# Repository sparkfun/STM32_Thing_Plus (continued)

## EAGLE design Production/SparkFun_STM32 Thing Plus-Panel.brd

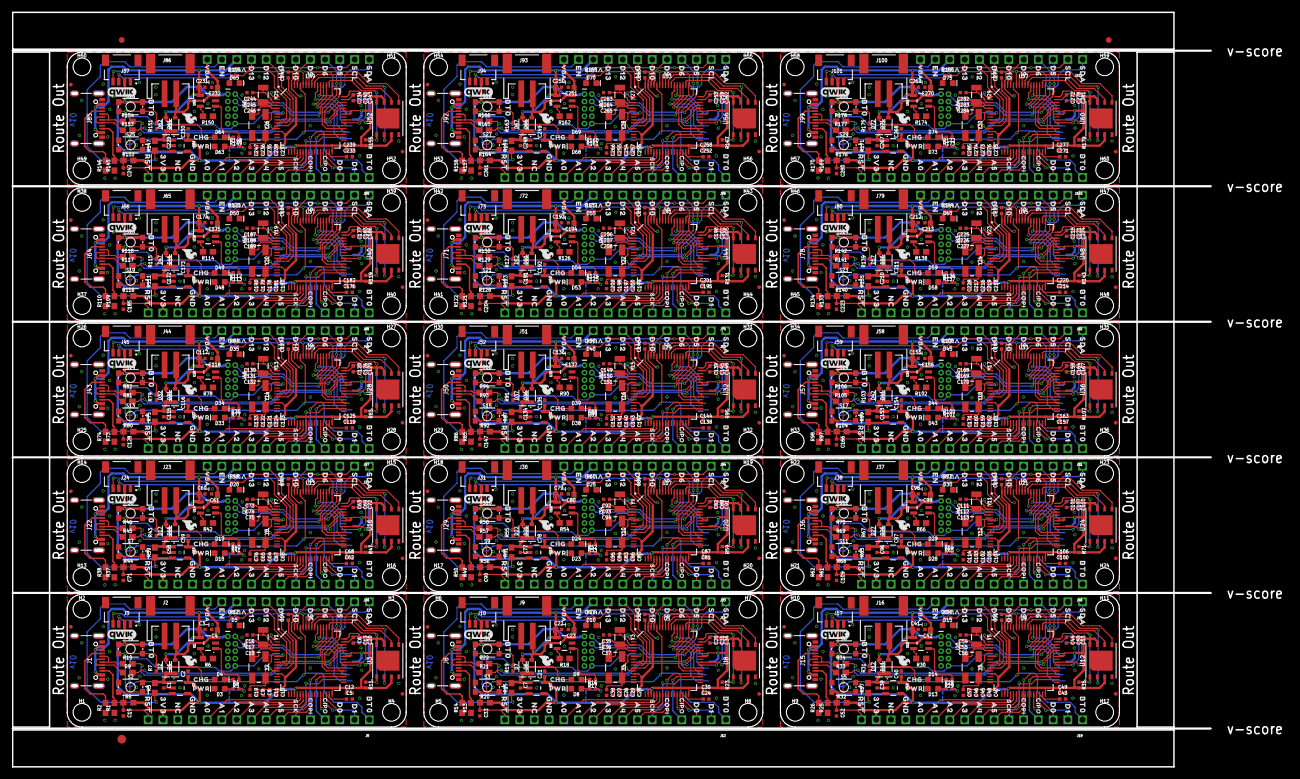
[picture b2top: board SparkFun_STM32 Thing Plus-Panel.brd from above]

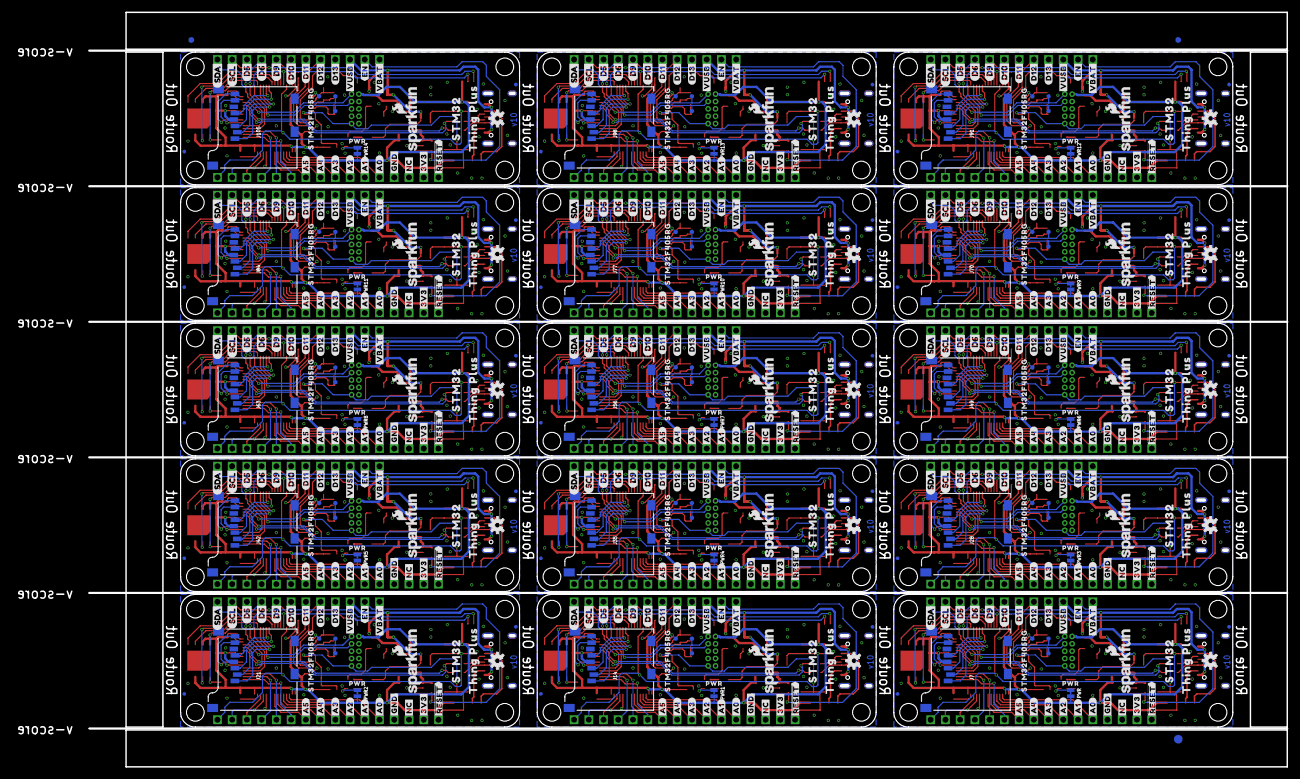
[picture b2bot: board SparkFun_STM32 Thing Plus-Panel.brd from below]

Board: 2 copper layers, 206.5 x 130.0 mm, 1866 parts (528 on the bottom side), 885 nets.

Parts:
C1, C2, C7, C9, C21, C27, C39, C40, C46, C58, C59, C65, C77, C78, C84, C96, C97, C103, C115, C116, C122, C134, C135, C141, C153, C154, C160, C172, C173, C179, C191, C192, C198, C210, C211, C217, C229, C230, C236, C248, C249, C255, C267, C268, C274: 1.0uF; 0402-TIGHT
C3, C4, C10, C22, C23, C28, C41, C42, C47, C60, C61, C66, C79, C80, C85, C98, C99, C104, C117, C118, C123, C136, C137, C142, C155, C156, C161, C174, C175, C180, C193, C194, C199, C212, C213, C218, C231, C232, C237, C250, C251, C256, C269, C270, C275: 4.7uF; 0402-TIGHT
C5, C6, C24, C25, C43, C44, C62, C63, C81, C82, C100, C101, C119, C120, C138, C139, C157, C158, C176, C177, C195, C196, C214, C215, C233, C234, C252, C253, C271, C272: 2.2uF; 0402-TIGHT
C8, C11, C12, C13, C14, C15, C20, C26, C29, C30, C31, C32, C33, C34, C45, C48, C49, C50, C51, C52, C53, C64, C67, C68, C69, C70, C71, C72, C83, C86, C87, C88, C89, C90, C91, C102, C105, C106, C107, C108, C109, C110, C121, C124, C125, C126, C127, C128, C129, C140, C143, C144, C145, C146, C147, C148, C159, C162, C163, C164, C165, C166, C167, C178, C181, C182, C183, C184, C185, C186, C197, C200, C201, C202, C203, C204, C205, C216, C219, C220, C221, C222, C223, C224, C235, C238, C239, C240, C241, C242, C243, C254, C257, C258, C259, C260, C261, C262, C273, C276, C277, C278, C279, C280, C281: 0.1uF; 0402-TIGHT
C16, C17, C35, C36, C54, C55, C73, C74, C92, C93, C111, C112, C130, C131, C149, C150, C168, C169, C187, C188, C206, C207, C225, C226, C244, C245, C263, C264, C282, C283: 15pF; 0402-TIGHT
C18, C19, C37, C38, C56, C57, C75, C76, C94, C95, C113, C114, C132, C133, C151, C152, C170, C171, C189, C190, C208, C209, C227, C228, C246, C247, C265, C266, C284, C285: 22pF; 0402-TIGHT
D1, D2, D6, D7, D11, D12, D16, D17, D21, D22, D26, D27, D31, D32, D36, D37, D41, D42, D46, D47, D51, D52, D56, D57, D61, D62, D66, D67, D71, D72: 3A/10V/280mV; SOD-323
D3, D8, D13, D18, D23, D28, D33, D38, D43, D48, D53, D58, D63, D68, D73: RED; LED-0603
D4, D9, D14, D19, D24, D29, D34, D39, D44, D49, D54, D59, D64, D69, D74: Yellow; LED-0603
D5, D10, D15, D20, D25, D30, D35, D40, D45, D50, D55, D60, D65, D70, D75: BLUE; LED-0603
E$1, E$2, E$3, E$4: FIDUCIAL-1X2
E$5, E$6: FIDUCIAL-1.5X3
FD1, FD2, FD3, FD4, FD5, FD6, FD7, FD8, FD9, FD10, FD11, FD12, FD13, FD14, FD15, FD16, FD17, FD18, FD19, FD20, FD21, FD22, FD23, FD24, FD25, FD26, FD27, FD28, FD29, FD30, FD31, FD32, FD33, FD34, FD35, FD36, FD37, FD38, FD39, FD40, FD41, FD42, FD43, FD44, FD45, FD46, FD47, FD48, FD49, FD50, FD51, FD52, FD53, FD54, FD55, FD56, FD57, FD58, FD59, FD60: FIDUCIALUFIDUCIAL; FIDUCIAL-MICRO
H1, H2, H3, H4, H5, H6, H7, H8, H9, H10, H11, H12, H13, H14, H15, H16, H17, H18, H19, H20, H21, H22, H23, H24, H25, H26, H27, H28, H29, H30, H31, H32, H33, H34, H35, H36, H37, H38, H39, H40, H41, H42, H43, H44, H45, H46, H47, H48, H49, H50, H51, H52, H53, H54, H55, H56, H57, H58, H59, H60: STAND-OFFTIGHT; STAND-OFF-TIGHT
J1, J8, J15, J22, J29, J36, J43, J50, J57, J64, J71, J78, J85, J92, J99: USB-C-16P-2LAYER-PADS
J2, J9, J16, J23, J30, J37, J44, J51, J58, J65, J72, J79, J86, J93, J100: JST-2-SMD
J3, J10, J17, J24, J31, J38, J45, J52, J59, J66, J73, J80, J87, J94, J101: QWIIC_RA; JST04_1MM_RA
J4, J11, J18, J25, J32, J39, J46, J53, J60, J67, J74, J81, J88, J95, J102: 1X12_SM_SQ_NOSILK
J5, J12, J19, J26, J33, J40, J47, J54, J61, J68, J75, J82, J89, J96, J103: 1X16_SM_SQ_NOSILK
J6, J13, J20, J27, J34, J41, J48, J55, J62, J69, J76, J83, J90, J97, J104: CORTEX_DEBUG; 2X5-PTH-1.27MM-NO_SILK
J7, J14, J21, J28, J35, J42, J49, J56, J63, J70, J77, J84, J91, J98, J105: MICRO-SD; MICRO-SD-SOCKET
LOGO1, LOGO4, LOGO7, LOGO10, LOGO13, LOGO16, LOGO19, LOGO22, LOGO25, LOGO28, LOGO31, LOGO34, LOGO37, LOGO40, LOGO43: QWIIC_LOGO_5MM; QWIIC_5MM
LOGO2, LOGO5, LOGO8, LOGO11, LOGO14, LOGO17, LOGO20, LOGO23, LOGO26, LOGO29, LOGO32, LOGO35, LOGO38, LOGO41, LOGO44: SFE_LOGO_NAME_FLAME.1_INCH; SFE_LOGO_NAME_FLAME_.1
LOGO3, LOGO6, LOGO9, LOGO12, LOGO15, LOGO18, LOGO21, LOGO24, LOGO27, LOGO30, LOGO33, LOGO36, LOGO39, LOGO42, LOGO45: OSHW-LOGOS; OSHW-LOGO-S
PWR, PWR1, PWR2, PWR3, PWR4, PWR5, PWR6, PWR7, PWR8, PWR9, PWR10, PWR11, PWR12, PWR13, PWR14: SMT-JUMPER_2_NC_TRACE_NO-SILK
R1, R2, R13, R14, R25, R26, R37, R38, R49, R50, R61, R62, R73, R74, R85, R86, R97, R98, R109, R110, R121, R122, R133, R134, R145, R146, R157, R158, R169, R170: 5.1k; 0603
R3, R15, R27, R39, R51, R63, R75, R87, R99, R111, R123, R135, R147, R159, R171: 10k; 0603
R4, R5, R12, R16, R17, R24, R28, R29, R36, R40, R41, R48, R52, R53, R60, R64, R65, R72, R76, R77, R84, R88, R89, R96, R100, R101, R108, R112, R113, R120, R124, R125, R132, R136, R137, R144, R148, R149, R156, R160, R161, R168, R172, R173, R180: 1k; 0402-TIGHT
R6, R18, R30, R42, R54, R66, R78, R90, R102, R114, R126, R138, R150, R162, R174: 2.0k; 0603
R7, R11, R19, R23, R31, R35, R43, R47, R55, R59, R67, R71, R79, R83, R91, R95, R103, R107, R115, R119, R127, R131, R139, R143, R151, R155, R163, R167, R175, R179: 100k; 0402-TIGHT
R8, R20, R32, R44, R56, R68, R80, R92, R104, R116, R128, R140, R152, R164, R176: 4.7k; 0603
R9, R10, R21, R22, R33, R34, R45, R46, R57, R58, R69, R70, R81, R82, R93, R94, R105, R106, R117, R118, R129, R130, R141, R142, R153, R154, R165, R166, R177, R178: 22; 0603
S1, S2, S3, S4, S5, S6, S7, S8, S9, S10, S11, S12, S13, S14, S15, S16, S17, S18, S19, S20, S21, S22, S23, S24, S25, S26, S27, S28, S29, S30: TACTILE_SWITCH_SMD_4.6X2.8MM
TP1, TP2, TP3, TP4, TP5, TP6, TP7, TP8, TP9, TP10, TP11, TP12, TP13, TP14, TP15, TP16, TP17, TP18, TP19, TP20, TP21, TP22, TP23, TP24, TP25, TP26, TP27, TP28, TP29, TP30: PAD.03X.03
U1, U6, U10, U14, U18, U22, U26, U30, U34, U38, U42, U46, U50, U54, U58: MCP73831; SOT23-5
U2, U7, U11, U15, U19, U23, U27, U31, U35, U39, U43, U47, U51, U55, U59: 3.3V; SOT23-5
U3, U8, U12, U16, U20, U24, U28, U32, U36, U40, U44, U48, U52, U56, U60: W25QXX128MBIT-6X5; WSON-8-6X5
U4, U5, U9, U13, U17, U21, U25, U29, U33, U37, U41, U45, U49, U53, U57: STM32F405RGT6; TQFP64
U$1, U$111, U$169, U$227, U$285, U$343, U$401, U$459, U$517, U$575, U$633, U$691, U$749, U$807, U$865: D53
U$2, U$17, U$117, U$175, U$233, U$291, U$349, U$407, U$465, U$523, U$581, U$639, U$697, U$755, U$813: #RST#0
U$3, U$49, U$90, U$97, U$148, U$155, U$206, U$213, U$264, U$271, U$322, U$329, U$380, U$387, U$438, U$445, U$496, U$503, U$554, U$561, U$612, U$619, U$670, U$677, U$728, U$735, U$786, U$793, U$844, U$851: BT00
U$4, U$18, U$118, U$176, U$234, U$292, U$350, U$408, U$466, U$524, U$582, U$640, U$698, U$756, U$814: D130
U$5, U$19, U$58, U$101, U$119, U$159, U$177, U$217, U$235, U$275, U$293, U$333, U$351, U$391, U$409, U$449, U$467, U$507, U$525, U$565, U$583, U$623, U$641, U$681, U$699, U$739, U$757, U$797, U$815, U$855: PWR0
U$6, U$20, U$120, U$178, U$236, U$294, U$352, U$410, U$468, U$526, U$584, U$642, U$700, U$758, U$816: CHG0
U$7, U$21, U$121, U$179, U$237, U$295, U$353, U$411, U$469, U$527, U$585, U$643, U$701, U$759, U$817: ##RESET##0
U$8, U$22, U$122, U$180, U$238, U$296, U$354, U$412, U$470, U$528, U$586, U$644, U$702, U$760, U$818: #3V3#0
U$9, U$28, U$123, U$181, U$239, U$297, U$355, U$413, U$471, U$529, U$587, U$645, U$703, U$761, U$819: #NC#0
U$10, U$66, U$124, U$182, U$240, U$298, U$356, U$414, U$472, U$530, U$588, U$646, U$704, U$762, U$820: #GND#0
U$11, U$67, U$125, U$183, U$241, U$299, U$357, U$415, U$473, U$531, U$589, U$647, U$705, U$763, U$821: #A0#0
U$12, U$68, U$126, U$184, U$242, U$300, U$358, U$416, U$474, U$532, U$590, U$648, U$706, U$764, U$822: #A1#0
U$13, U$69, U$127, U$185, U$243, U$301, U$359, U$417, U$475, U$533, U$591, U$649, U$707, U$765, U$823: #A2#0
U$14, U$70, U$128, U$186, U$244, U$302, U$360, U$418, U$476, U$534, U$592, U$650, U$708, U$766, U$824: #A3#0
U$15, U$71, U$129, U$187, U$245, U$303, U$361, U$419, U$477, U$535, U$593, U$651, U$709, U$767, U$825: #A4#0
U$16, U$72, U$130, U$188, U$246, U$304, U$362, U$420, U$478, U$536, U$594, U$652, U$710, U$768, U$826: #A5#0
U$23, U$112, U$170, U$228, U$286, U$344, U$402, U$460, U$518, U$576, U$634, U$692, U$750, U$808, U$866: D62
U$24, U$113, U$171, U$229, U$287, U$345, U$403, U$461, U$519, U$577, U$635, U$693, U$751, U$809, U$867: D91
U$25, U$55, U$94, U$114, U$152, U$172, U$210, U$230, U$268, U$288, U$326, U$346, U$384, U$404, U$442, U$462, U$500, U$520, U$558, U$578, U$616, U$636, U$674, U$694, U$732, U$752, U$790, U$810, U$848, U$868: D100
U$26, U$115, U$173, U$231, U$289, U$347, U$405, U$463, U$521, U$579, U$637, U$695, U$753, U$811, U$869: SCL4
U$27, U$116, U$174, U$232, U$290, U$348, U$406, U$464, U$522, U$580, U$638, U$696, U$754, U$812, U$870: SDA5
U$29, U$73, U$131, U$189, U$247, U$305, U$363, U$421, U$479, U$537, U$595, U$653, U$711, U$769, U$827: #D11#0
U$30, U$74, U$132, U$190, U$248, U$306, U$364, U$422, U$480, U$538, U$596, U$654, U$712, U$770, U$828: #D12#0
U$31, U$75, U$133, U$191, U$249, U$307, U$365, U$423, U$481, U$539, U$597, U$655, U$713, U$771, U$829: #D13#0
U$32, U$76, U$134, U$192, U$250, U$308, U$366, U$424, U$482, U$540, U$598, U$656, U$714, U$772, U$830: #VUSB#0
U$33, U$77, U$135, U$193, U$251, U$309, U$367, U$425, U$483, U$541, U$599, U$657, U$715, U$773, U$831: #EN#0
U$34, U$78, U$136, U$194, U$252, U$310, U$368, U$426, U$484, U$542, U$600, U$658, U$716, U$774, U$832: #VBAT#0
U$35, U$79, U$137, U$195, U$253, U$311, U$369, U$427, U$485, U$543, U$601, U$659, U$717, U$775, U$833: 3V30
U$36, U$80, U$138, U$196, U$254, U$312, U$370, U$428, U$486, U$544, U$602, U$660, U$718, U$776, U$834: NC0
U$37, U$81, U$139, U$197, U$255, U$313, U$371, U$429, U$487, U$545, U$603, U$661, U$719, U$777, U$835: GND0
U$38, U$82, U$140, U$198, U$256, U$314, U$372, U$430, U$488, U$546, U$604, U$662, U$720, U$778, U$836: A00
U$39, U$83, U$141, U$199, U$257, U$315, U$373, U$431, U$489, U$547, U$605, U$663, U$721, U$779, U$837: A10
U$40, U$84, U$142, U$200, U$258, U$316, U$374, U$432, U$490, U$548, U$606, U$664, U$722, U$780, U$838: A20
U$41, U$85, U$143, U$201, U$259, U$317, U$375, U$433, U$491, U$549, U$607, U$665, U$723, U$781, U$839: A30
U$42, U$86, U$144, U$202, U$260, U$318, U$376, U$434, U$492, U$550, U$608, U$666, U$724, U$782, U$840: A40
U$43, U$87, U$145, U$203, U$261, U$319, U$377, U$435, U$493, U$551, U$609, U$667, U$725, U$783, U$841: A50
U$44, U$98, U$156, U$214, U$272, U$330, U$388, U$446, U$504, U$562, U$620, U$678, U$736, U$794, U$852: SCK0
U$45, U$99, U$157, U$215, U$273, U$331, U$389, U$447, U$505, U$563, U$621, U$679, U$737, U$795, U$853: COPI0
U$46, U$100, U$158, U$216, U$274, U$332, U$390, U$448, U$506, U$564, U$622, U$680, U$738, U$796, U$854: CIPO0
U$47, U$88, U$146, U$204, U$262, U$320, U$378, U$436, U$494, U$552, U$610, U$668, U$726, U$784, U$842: D00
U$48, U$89, U$147, U$205, U$263, U$321, U$379, U$437, U$495, U$553, U$611, U$669, U$727, U$785, U$843: D10
U$50, U$104, U$162, U$220, U$278, U$336, U$394, U$452, U$510, U$568, U$626, U$684, U$742, U$800, U$858: VBAT_0
U$51, U$105, U$163, U$221, U$279, U$337, U$395, U$453, U$511, U$569, U$627, U$685, U$743, U$801, U$859: EN_0
U$52, U$91, U$149, U$207, U$265, U$323, U$381, U$439, U$497, U$555, U$613, U$671, U$729, U$787, U$845: D50
U$53, U$92, U$150, U$208, U$266, U$324, U$382, U$440, U$498, U$556, U$614, U$672, U$730, U$788, U$846: D60
U$54, U$93, U$151, U$209, U$267, U$325, U$383, U$441, U$499, U$557, U$615, U$673, U$731, U$789, U$847: D90
U$56, U$95, U$153, U$211, U$269, U$327, U$385, U$443, U$501, U$559, U$617, U$675, U$733, U$791, U$849: D110
U$57, U$96, U$154, U$212, U$270, U$328, U$386, U$444, U$502, U$560, U$618, U$676, U$734, U$792, U$850: D120
U$59, U$102, U$160, U$218, U$276, U$334, U$392, U$450, U$508, U$566, U$624, U$682, U$740, U$798, U$856: SCL_0
U$60, U$103, U$161, U$219, U$277, U$335, U$393, U$451, U$509, U$567, U$625, U$683, U$741, U$799, U$857: SDA_0
U$61, U$106, U$164, U$222, U$280, U$338, U$396, U$454, U$512, U$570, U$628, U$686, U$744, U$802, U$860: VUSB0
U$62, U$107, U$165, U$223, U$281, U$339, U$397, U$455, U$513, U$571, U$629, U$687, U$745, U$803, U$861: STM320
U$63, U$108, U$166, U$224, U$282, U$340, U$398, U$456, U$514, U$572, U$630, U$688, U$746, U$804, U$862: THING_PLUS0
U$64, U$109, U$167, U$225, U$283, U$341, U$399, U$457, U$515, U$573, U$631, U$689, U$747, U$805, U$863: STM32F405RG0
U$65, U$110, U$168, U$226, U$284, U$342, U$400, U$458, U$516, U$574, U$632, U$690, U$748, U$806, U$864: SFE_LOGO_FLAME_.1
VB, VB1, VB2, VB3, VB4, VB5, VB6, VB7, VB8, VB9, VB10, VB11, VB12, VB13, VB14: PAD.03X.03
Y1, Y3, Y5, Y7, Y9, Y11, Y13, Y15, Y17, Y19, Y21, Y23, Y25, Y27, Y29: 32.768kHz; CRYSTAL-SMD-3.2X1.5MM
Y2, Y4, Y6, Y8, Y10, Y12, Y14, Y16, Y18, Y20, Y22, Y24, Y26, Y28, Y30: 12MHz; CRYSTAL-SMD-5X3.2-4PAD

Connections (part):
3.3V: C2.1, C8.1, C9.1, C10.1, C11.1, C12.1, C13.1, C14.1, C20.1, J3.2, J5.15, J6.1, J7.VCC, PWR.2, R8.2, R11.2, S1.3, S1.4, U2.5, U3.3, U3.7, U3.8, U4.13, U4.19, U4.32, U4.42, U4.43, U4.48, U4.64
3.3V1: C21.1, C26.1, C27.1, C28.1, C29.1, C30.1, C31.1, C32.1, C34.1, J10.2, J12.15, J13.1, J14.VCC, PWR1.2, R20.2, R23.2, S4.3, S4.4, U5.13, U5.19, U5.32, U5.42, U5.43, U5.48, U5.64, U7.5, U8.3, U8.7, U8.8
3.3V2: C40.1, C45.1, C46.1, C47.1, C48.1, C49.1, C50.1, C51.1, C53.1, J17.2, J19.15, J20.1, J21.VCC, PWR2.2, R32.2, R35.2, S6.3, S6.4, U9.13, U9.19, U9.32, U9.42, U9.43, U9.48, U9.64, U11.5, U12.3, U12.7, U12.8
3.3V3: C59.1, C64.1, C65.1, C66.1, C67.1, C68.1, C69.1, C70.1, C72.1, J24.2, J26.15, J27.1, J28.VCC, PWR3.2, R44.2, R47.2, S8.3, S8.4, U13.13, U13.19, U13.32, U13.42, U13.43, U13.48, U13.64, U15.5, U16.3, U16.7, U16.8
3.3V4: C78.1, C83.1, C84.1, C85.1, C86.1, C87.1, C88.1, C89.1, C91.1, J31.2, J33.15, J34.1, J35.VCC, PWR4.2, R56.2, R59.2, S10.3, S10.4, U17.13, U17.19, U17.32, U17.42, U17.43, U17.48, U17.64, U19.5, U20.3, U20.7, U20.8
3.3V5: C97.1, C102.1, C103.1, C104.1, C105.1, C106.1, C107.1, C108.1, C110.1, J38.2, J40.15, J41.1, J42.VCC, PWR5.2, R68.2, R71.2, S12.3, S12.4, U21.13, U21.19, U21.32, U21.42, U21.43, U21.48, U21.64, U23.5, U24.3, U24.7, U24.8
3.3V6: C116.1, C121.1, C122.1, C123.1, C124.1, C125.1, C126.1, C127.1, C129.1, J45.2, J47.15, J48.1, J49.VCC, PWR6.2, R80.2, R83.2, S14.3, S14.4, U25.13, U25.19, U25.32, U25.42, U25.43, U25.48, U25.64, U27.5, U28.3, U28.7, U28.8
3.3V7: C135.1, C140.1, C141.1, C142.1, C143.1, C144.1, C145.1, C146.1, C148.1, J52.2, J54.15, J55.1, J56.VCC, PWR7.2, R92.2, R95.2, S16.3, S16.4, U29.13, U29.19, U29.32, U29.42, U29.43, U29.48, U29.64, U31.5, U32.3, U32.7, U32.8
3.3V8: C154.1, C159.1, C160.1, C161.1, C162.1, C163.1, C164.1, C165.1, C167.1, J59.2, J61.15, J62.1, J63.VCC, PWR8.2, R104.2, R107.2, S18.3, S18.4, U33.13, U33.19, U33.32, U33.42, U33.43, U33.48, U33.64, U35.5, U36.3, U36.7, U36.8
3.3V9: C173.1, C178.1, C179.1, C180.1, C181.1, C182.1, C183.1, C184.1, C186.1, J66.2, J68.15, J69.1, J70.VCC, PWR9.2, R116.2, R119.2, S20.3, S20.4, U37.13, U37.19, U37.32, U37.42, U37.43, U37.48, U37.64, U39.5, U40.3, U40.7, U40.8
3.3V10: C192.1, C197.1, C198.1, C199.1, C200.1, C201.1, C202.1, C203.1, C205.1, J73.2, J75.15, J76.1, J77.VCC, PWR10.2, R128.2, R131.2, S22.3, S22.4, U41.13, U41.19, U41.32, U41.42, U41.43, U41.48, U41.64, U43.5, U44.3, U44.7, U44.8
3.3V11: C211.1, C216.1, C217.1, C218.1, C219.1, C220.1, C221.1, C222.1, C224.1, J80.2, J82.15, J83.1, J84.VCC, PWR11.2, R140.2, R143.2, S24.3, S24.4, U45.13, U45.19, U45.32, U45.42, U45.43, U45.48, U45.64, U47.5, U48.3, U48.7, U48.8
3.3V12: C230.1, C235.1, C236.1, C237.1, C238.1, C239.1, C240.1, C241.1, C243.1, J87.2, J89.15, J90.1, J91.VCC, PWR12.2, R152.2, R155.2, S26.3, S26.4, U49.13, U49.19, U49.32, U49.42, U49.43, U49.48, U49.64, U51.5, U52.3, U52.7, U52.8
3.3V13: C249.1, C254.1, C255.1, C256.1, C257.1, C258.1, C259.1, C260.1, C262.1, J94.2, J96.15, J97.1, J98.VCC, PWR13.2, R164.2, R167.2, S28.3, S28.4, U53.13, U53.19, U53.32, U53.42, U53.43, U53.48, U53.64, U55.5, U56.3, U56.7, U56.8
3.3V14: C268.1, C273.1, C274.1, C275.1, C276.1, C277.1, C278.1, C279.1, C281.1, J101.2, J103.15, J104.1, J105.VCC, PWR14.2, R176.2, R179.2, S30.3, S30.4, U57.13, U57.19, U57.32, U57.42, U57.43, U57.48, U57.64, U59.5, U60.3, U60.7, U60.8
32KHZ_IN: C16.1, U4.3, Y1.P$1
32KHZ_IN1: C35.1, U5.3, Y3.P$1
32KHZ_IN2: C54.1, U9.3, Y5.P$1
32KHZ_IN3: C73.1, U13.3, Y7.P$1
32KHZ_IN4: C92.1, U17.3, Y9.P$1
32KHZ_IN5: C111.1, U21.3, Y11.P$1
32KHZ_IN6: C130.1, U25.3, Y13.P$1
32KHZ_IN7: C149.1, U29.3, Y15.P$1
32KHZ_IN8: C168.1, U33.3, Y17.P$1
32KHZ_IN9: C187.1, U37.3, Y19.P$1
32KHZ_IN10: C206.1, U41.3, Y21.P$1
32KHZ_IN11: C225.1, U45.3, Y23.P$1
32KHZ_IN12: C244.1, U49.3, Y25.P$1
32KHZ_IN13: C263.1, U53.3, Y27.P$1
32KHZ_IN14: C282.1, U57.3, Y29.P$1
32KHZ_OUT: C17.1, U4.4, Y1.P$2
32KHZ_OUT1: C36.1, U5.4, Y3.P$2
32KHZ_OUT2: C55.1, U9.4, Y5.P$2
32KHZ_OUT3: C74.1, U13.4, Y7.P$2
32KHZ_OUT4: C93.1, U17.4, Y9.P$2
32KHZ_OUT5: C112.1, U21.4, Y11.P$2
32KHZ_OUT6: C131.1, U25.4, Y13.P$2
32KHZ_OUT7: C150.1, U29.4, Y15.P$2
32KHZ_OUT8: C169.1, U33.4, Y17.P$2
32KHZ_OUT9: C188.1, U37.4, Y19.P$2
32KHZ_OUT10: C207.1, U41.4, Y21.P$2
32KHZ_OUT11: C226.1, U45.4, Y23.P$2
32KHZ_OUT12: C245.1, U49.4, Y25.P$2
32KHZ_OUT13: C264.1, U53.4, Y27.P$2
32KHZ_OUT14: C283.1, U57.4, Y29.P$2
!RESET: C15.1, J5.16, J6.10, R8.1, S2.1, S2.2, U4.7
!RESET1: C33.1, J12.16, J13.10, R20.1, S3.1, S3.2, U5.7
!RESET2: C52.1, J19.16, J20.10, R32.1, S5.1, S5.2, U9.7
!RESET3: C71.1, J26.16, J27.10, R44.1, S7.1, S7.2, U13.7
!RESET4: C90.1, J33.16, J34.10, R56.1, S9.1, S9.2, U17.7
!RESET5: C109.1, J40.16, J41.10, R68.1, S11.1, S11.2, U21.7
!RESET6: C128.1, J47.16, J48.10, R80.1, S13.1, S13.2, U25.7
!RESET7: C147.1, J54.16, J55.10, R92.1, S15.1, S15.2, U29.7
!RESET8: C166.1, J61.16, J62.10, R104.1, S17.1, S17.2, U33.7
!RESET9: C185.1, J68.16, J69.10, R116.1, S19.1, S19.2, U37.7
!RESET10: C204.1, J75.16, J76.10, R128.1, S21.1, S21.2, U41.7
!RESET11: C223.1, J82.16, J83.10, R140.1, S23.1, S23.2, U45.7
!RESET12: C242.1, J89.16, J90.10, R152.1, S25.1, S25.2, U49.7
!RESET13: C261.1, J96.16, J97.10, R164.1, S27.1, S27.2, U53.7
!RESET14: C280.1, J103.16, J104.10, R176.1, S29.1, S29.2, U57.7
A0: J5.12, U4.20
A1: J5.11, U4.21
A2: J5.10, U4.22
A3: J5.9, U4.23
A4: J5.8, U4.24
A5: J5.7, U4.25
A6: J12.12, U5.20
A7: J12.11, U5.21
A8: J12.10, U5.22
A9: J12.9, U5.23
A10: J12.8, U5.24
A11: J12.7, U5.25
A12: J19.12, U9.20
A13: J19.11, U9.21
A14: J19.10, U9.22
A15: J19.9, U9.23
A16: J19.8, U9.24
A17: J19.7, U9.25
A18: J26.12, U13.20
A19: J26.11, U13.21
A20: J26.10, U13.22
A21: J26.9, U13.23
A22: J26.8, U13.24
A23: J26.7, U13.25
A24: J33.12, U17.20
A25: J33.11, U17.21
A26: J33.10, U17.22
A27: J33.9, U17.23
A28: J33.8, U17.24
A29: J33.7, U17.25
A30: J40.12, U21.20
A31: J40.11, U21.21
A32: J40.10, U21.22
A33: J40.9, U21.23
A34: J40.8, U21.24
A35: J40.7, U21.25
A36: J47.12, U25.20
A37: J47.11, U25.21
A38: J47.10, U25.22
A39: J47.9, U25.23
A40: J47.8, U25.24
A41: J47.7, U25.25
A42: J54.12, U29.20
A43: J54.11, U29.21
A44: J54.10, U29.22
A45: J54.9, U29.23
A46: J54.8, U29.24
A47: J54.7, U29.25
A48: J61.12, U33.20
A49: J61.11, U33.21
A50: J61.10, U33.22
A51: J61.9, U33.23
A52: J61.8, U33.24
A53: J61.7, U33.25
A54: J68.12, U37.20
A55: J68.11, U37.21
A56: J68.10, U37.22
A57: J68.9, U37.23
A58: J68.8, U37.24
A59: J68.7, U37.25
A60: J75.12, U41.20
A61: J75.11, U41.21
A62: J75.10, U41.22
A63: J75.9, U41.23
A64: J75.8, U41.24
A65: J75.7, U41.25
A66: J82.12, U45.20
A67: J82.11, U45.21
A68: J82.10, U45.22
A69: J82.9, U45.23
A70: J82.8, U45.24
A71: J82.7, U45.25
A72: J89.12, U49.20
A73: J89.11, U49.21
A74: J89.10, U49.22
A75: J89.9, U49.23
A76: J89.8, U49.24
A77: J89.7, U49.25
A78: J96.12, U53.20
A79: J96.11, U53.21
A80: J96.10, U53.22
A81: J96.9, U53.23
A82: J96.8, U53.24
A83: J96.7, U53.25
A84: J103.12, U57.20
A85: J103.11, U57.21
A86: J103.10, U57.22
A87: J103.9, U57.23
A88: J103.8, U57.24
A89: J103.7, U57.25
BOOT0: J5.1, R7.2, S1.1, S1.2, U4.60
BOOT1: J12.1, R19.2, S4.1, S4.2, U5.60
BOOT2: J19.1, R31.2, S6.1, S6.2, U9.60
BOOT3: J26.1, R43.2, S8.1, S8.2, U13.60
BOOT4: J33.1, R55.2, S10.1, S10.2, U17.60
BOOT5: J40.1, R67.2, S12.1, S12.2, U21.60
BOOT6: J47.1, R79.2, S14.1, S14.2, U25.60
BOOT7: J54.1, R91.2, S16.1, S16.2, U29.60
BOOT8: J61.1, R103.2, S18.1, S18.2, U33.60
BOOT9: J68.1, R115.2, S20.1, S20.2, U37.60
BOOT10: J75.1, R127.2, S22.1, S22.2, U41.60
BOOT11: J82.1, R139.2, S24.1, S24.2, U45.60
BOOT12: J89.1, R151.2, S26.1, S26.2, U49.60
BOOT13: J96.1, R163.2, S28.1, S28.2, U53.60
BOOT14: J103.1, R175.2, S30.1, S30.2, U57.60
CIPO: J5.4, U4.35
CIPO1: J12.4, U5.35
CIPO2: J19.4, U9.35
CIPO3: J26.4, U13.35
CIPO4: J33.4, U17.35
CIPO5: J40.4, U21.35
CIPO6: J47.4, U25.35
CIPO7: J54.4, U29.35
CIPO8: J61.4, U33.35
CIPO9: J68.4, U37.35
CIPO10: J75.4, U41.35
CIPO11: J82.4, U45.35
CIPO12: J89.4, U49.35
CIPO13: J96.4, U53.35
CIPO14: J103.4, U57.35
COPI: J5.5, U4.36
COPI1: J12.5, U5.36
COPI2: J19.5, U9.36
COPI3: J26.5, U13.36
COPI4: J33.5, U17.36
COPI5: J40.5, U21.36
COPI6: J47.5, U25.36
COPI7: J54.5, U29.36
COPI8: J61.5, U33.36
COPI9: J68.5, U37.36
COPI10: J75.5, U41.36
COPI11: J82.5, U45.36
COPI12: J89.5, U49.36
COPI13: J96.5, U53.36
COPI14: J103.5, U57.36
D0/RX: J5.3, U4.30
D0/RX1: J12.3, U5.30
D0/RX2: J19.3, U9.30
D0/RX3: J26.3, U13.30
D0/RX4: J33.3, U17.30
D0/RX5: J40.3, U21.30
D0/RX6: J47.3, U25.30
D0/RX7: J54.3, U29.30
D0/RX8: J61.3, U33.30
D0/RX9: J68.3, U37.30
D0/RX10: J75.3, U41.30
D0/RX11: J82.3, U45.30
D0/RX12: J89.3, U49.30
D0/RX13: J96.3, U53.30
D0/RX14: J103.3, U57.30
D1: J11.9, R24.2, U5.9
D1/TX: J5.2, U4.29
D1/TX1: J12.2, U5.29
D1/TX2: J19.2, U9.29
D1/TX3: J26.2, U13.29
D1/TX4: J33.2, U17.29
D1/TX5: J40.2, U21.29
D1/TX6: J47.2, U25.29
D1/TX7: J54.2, U29.29
D1/TX8: J61.2, U33.29
D1/TX9: J68.2, U37.29
D1/TX10: J75.2, U41.29
D1/TX11: J82.2, U45.29
D1/TX12: J89.2, U49.29
D1/TX13: J96.2, U53.29
D1/TX14: J103.2, U57.29
D2: J11.8, U5.10
D3: J11.7, U5.11
D4: J11.6, U5.62
D5: J4.3, U4.38
D6: J4.4, U4.37
D7: J11.5, U5.61
D8: J11.4, U5.37
D9: J4.5, U4.61
D10: J4.6, U4.62
D11: J4.7, U4.11
D12: J4.8, U4.10
D13: J4.9, R12.2, U4.9
D14: J11.3, U5.38
D15: J18.9, R36.2, U9.9
D16: J18.8, U9.10
D17: J18.7, U9.11
D18: J18.6, U9.62
D19: J18.5, U9.61
D20: J18.4, U9.37
D21: J18.3, U9.38
D22: J25.9, R48.2, U13.9
D23: J25.8, U13.10
D24: J25.7, U13.11
D25: J25.6, U13.62
D26: J25.5, U13.61
D27: J25.4, U13.37
D28: J25.3, U13.38
D29: J32.9, R60.2, U17.9
D30: J32.8, U17.10
D31: J32.7, U17.11
D32: J32.6, U17.62
D33: J32.5, U17.61
D34: J32.4, U17.37
D35: J32.3, U17.38
D36: J39.9, R72.2, U21.9
D37: J39.8, U21.10
D38: J39.7, U21.11
D39: J39.6, U21.62
D40: J39.5, U21.61
D41: J39.4, U21.37
D42: J39.3, U21.38
D43: J46.9, R84.2, U25.9
D44: J46.8, U25.10
D45: J46.7, U25.11
D46: J46.6, U25.62
D47: J46.5, U25.61
D48: J46.4, U25.37
D49: J46.3, U25.38
D50: J53.9, R96.2, U29.9
D51: J53.8, U29.10
D52: J53.7, U29.11
D53: J53.6, U29.62
D54: J53.5, U29.61
D55: J53.4, U29.37
D56: J53.3, U29.38
D57: J60.9, R108.2, U33.9
D58: J60.8, U33.10
D59: J60.7, U33.11
D60: J60.6, U33.62
D61: J60.5, U33.61
D62: J60.4, U33.37
D63: J60.3, U33.38
D64: J67.9, R120.2, U37.9
D65: J67.8, U37.10
D66: J67.7, U37.11
D67: J67.6, U37.62
D68: J67.5, U37.61
D69: J67.4, U37.37
D70: J67.3, U37.38
D71: J74.9, R132.2, U41.9
D72: J74.8, U41.10
D73: J74.7, U41.11
D74: J74.6, U41.62
D75: J74.5, U41.61
D76: J74.4, U41.37
D77: J74.3, U41.38
D78: J81.9, R144.2, U45.9
D79: J81.8, U45.10
D80: J81.7, U45.11
D81: J81.6, U45.62
D82: J81.5, U45.61
D83: J81.4, U45.37
D84: J81.3, U45.38
D85: J88.9, R156.2, U49.9
D86: J88.8, U49.10
D87: J88.7, U49.11
D88: J88.6, U49.62
D89: J88.5, U49.61
D90: J88.4, U49.37
D91: J88.3, U49.38
D92: J95.9, R168.2, U53.9
D93: J95.8, U53.10
D94: J95.7, U53.11
D95: J95.6, U53.62
D96: J95.5, U53.61
D97: J95.4, U53.37
D98: J95.3, U53.38
D99: J102.9, R180.2, U57.9
D100: J102.8, U57.10
D101: J102.7, U57.11
D102: J102.6, U57.62
D103: J102.5, U57.61
D104: J102.4, U57.37
D105: J102.3, U57.38
D+: R9.2, U4.45
D+1: R21.2, U5.45
D+2: R33.2, U9.45
D+3: R45.2, U13.45
D+4: R57.2, U17.45
D+5: R69.2, U21.45
D+6: R81.2, U25.45
D+7: R93.2, U29.45
D+8: R105.2, U33.45
D+9: R117.2, U37.45
D+10: R129.2, U41.45
D+11: R141.2, U45.45
D+12: R153.2, U49.45
D+13: R165.2, U53.45
D+14: R177.2, U57.45
D-: R10.2, U4.44
D-1: R22.2, U5.44
D-2: R34.2, U9.44
D-3: R46.2, U13.44
D-4: R58.2, U17.44
D-5: R70.2, U21.44
D-6: R82.2, U25.44
D-7: R94.2, U29.44
D-8: R106.2, U33.44
D-9: R118.2, U37.44
D-10: R130.2, U41.44
D-11: R142.2, U45.44
D-12: R154.2, U49.44
D-13: R166.2, U53.44
D-14: R178.2, U57.44
EN: J4.11, R3.1, U2.3
EN1: J11.11, R15.1, U7.3
EN2: J18.11, R27.1, U11.3
EN3: J25.11, R39.1, U15.3
EN4: J32.11, R51.1, U19.3
EN5: J39.11, R63.1, U23.3
EN6: J46.11, R75.1, U27.3
EN7: J53.11, R87.1, U31.3
EN8: J60.11, R99.1, U35.3
EN9: J67.11, R111.1, U39.3
EN10: J74.11, R123.1, U43.3
EN11: J81.11, R135.1, U47.3
EN12: J88.11, R147.1, U51.3
EN13: J95.11, R159.1, U55.3
EN14: J102.11, R171.1, U59.3
FLASH_!CS: R11.1, U3.1, U4.50
FLASH_!CS1: R23.1, U5.50, U8.1
FLASH_!CS2: R35.1, U9.50, U12.1
FLASH_!CS3: R47.1, U13.50, U16.1
FLASH_!CS4: R59.1, U17.50, U20.1
FLASH_!CS5: R71.1, U21.50, U24.1
FLASH_!CS6: R83.1, U25.50, U28.1
FLASH_!CS7: R95.1, U29.50, U32.1
FLASH_!CS8: R107.1, U33.50, U36.1
FLASH_!CS9: R119.1, U37.50, U40.1
FLASH_!CS10: R131.1, U41.50, U44.1
FLASH_!CS11: R143.1, U45.50, U48.1
FLASH_!CS12: R155.1, U49.50, U52.1
FLASH_!CS13: R167.1, U53.50, U56.1
FLASH_!CS14: R179.1, U57.50, U60.1
FLASH_SCK: U3.6, U4.55
FLASH_SCK1: U5.55, U8.6
FLASH_SCK2: U9.55, U12.6
FLASH_SCK3: U13.55, U16.6
FLASH_SCK4: U17.55, U20.6
FLASH_SCK5: U21.55, U24.6
FLASH_SCK6: U25.55, U28.6
FLASH_SCK7: U29.55, U32.6
FLASH_SCK8: U33.55, U36.6
FLASH_SCK9: U37.55, U40.6
FLASH_SCK10: U41.55, U44.6
FLASH_SCK11: U45.55, U48.6
FLASH_SCK12: U49.55, U52.6
FLASH_SCK13: U53.55, U56.6
FLASH_SCK14: U57.55, U60.6
FLASH_SDI: U3.5, U4.57
FLASH_SDI1: U5.57, U8.5
FLASH_SDI2: U9.57, U12.5
FLASH_SDI3: U13.57, U16.5
FLASH_SDI4: U17.57, U20.5
FLASH_SDI5: U21.57, U24.5
FLASH_SDI6: U25.57, U28.5
FLASH_SDI7: U29.57, U32.5
FLASH_SDI8: U33.57, U36.5
FLASH_SDI9: U37.57, U40.5
FLASH_SDI10: U41.57, U44.5
FLASH_SDI11: U45.57, U48.5
FLASH_SDI12: U49.57, U52.5
FLASH_SDI13: U53.57, U56.5
FLASH_SDI14: U57.57, U60.5
FLASH_SDO: U3.2, U4.56
FLASH_SDO1: U5.56, U8.2
FLASH_SDO2: U9.56, U12.2
FLASH_SDO3: U13.56, U16.2
FLASH_SDO4: U17.56, U20.2
FLASH_SDO5: U21.56, U24.2
FLASH_SDO6: U25.56, U28.2
FLASH_SDO7: U29.56, U32.2
FLASH_SDO8: U33.56, U36.2
FLASH_SDO9: U37.56, U40.2
FLASH_SDO10: U41.56, U44.2
FLASH_SDO11: U45.56, U48.2
FLASH_SDO12: U49.56, U52.2
FLASH_SDO13: U53.56, U56.2
FLASH_SDO14: U57.56, U60.2
GND: C1.2, C2.2, C3.2, C4.2, C5.2, C6.2, C8.2, C9.2, C10.2, C11.2, C12.2, C13.2, C14.2, C15.2, C16.2, C17.2, C18.2, C19.2, C20.2, D3.C, D5.C, J1.GND, J1.GND2, J1.SHLD1, J1.SHLD2, J1.SHLD3, J1.SHLD4, J2.1, J3.1, J5.13, J6.3, J6.5, J6.9, J7.CD1, J7.GND, J7.GND1, J7.GND3, R1.1, R2.1, R6.1, R7.1, S2.3, S2.4, U1.2, U2.2, U3.4, U4.12, U4.18, U4.28, U4.63
GND1: C7.2, C21.2, C22.2, C23.2, C24.2, C25.2, C26.2, C27.2, C28.2, C29.2, C30.2, C31.2, C32.2, C33.2, C34.2, C35.2, C36.2, C37.2, C38.2, D8.C, D10.C, J8.GND, J8.GND2, J8.SHLD1, J8.SHLD2, J8.SHLD3, J8.SHLD4, J9.1, J10.1, J12.13, J13.3, J13.5, J13.9, J14.CD1, J14.GND, J14.GND1, J14.GND3, R13.1, R14.1, R18.1, R19.1, S3.3, S3.4, U5.12, U5.18, U5.28, U5.63, U6.2, U7.2, U8.4
GND2: C39.2, C40.2, C41.2, C42.2, C43.2, C44.2, C45.2, C46.2, C47.2, C48.2, C49.2, C50.2, C51.2, C52.2, C53.2, C54.2, C55.2, C56.2, C57.2, D13.C, D15.C, J15.GND, J15.GND2, J15.SHLD1, J15.SHLD2, J15.SHLD3, J15.SHLD4, J16.1, J17.1, J19.13, J20.3, J20.5, J20.9, J21.CD1, J21.GND, J21.GND1, J21.GND3, R25.1, R26.1, R30.1, R31.1, S5.3, S5.4, U9.12, U9.18, U9.28, U9.63, U10.2, U11.2, U12.4
GND3: C58.2, C59.2, C60.2, C61.2, C62.2, C63.2, C64.2, C65.2, C66.2, C67.2, C68.2, C69.2, C70.2, C71.2, C72.2, C73.2, C74.2, C75.2, C76.2, D18.C, D20.C, J22.GND, J22.GND2, J22.SHLD1, J22.SHLD2, J22.SHLD3, J22.SHLD4, J23.1, J24.1, J26.13, J27.3, J27.5, J27.9, J28.CD1, J28.GND, J28.GND1, J28.GND3, R37.1, R38.1, R42.1, R43.1, S7.3, S7.4, U13.12, U13.18, U13.28, U13.63, U14.2, U15.2, U16.4
GND4: C77.2, C78.2, C79.2, C80.2, C81.2, C82.2, C83.2, C84.2, C85.2, C86.2, C87.2, C88.2, C89.2, C90.2, C91.2, C92.2, C93.2, C94.2, C95.2, D23.C, D25.C, J29.GND, J29.GND2, J29.SHLD1, J29.SHLD2, J29.SHLD3, J29.SHLD4, J30.1, J31.1, J33.13, J34.3, J34.5, J34.9, J35.CD1, J35.GND, J35.GND1, J35.GND3, R49.1, R50.1, R54.1, R55.1, S9.3, S9.4, U17.12, U17.18, U17.28, U17.63, U18.2, U19.2, U20.4
GND5: C96.2, C97.2, C98.2, C99.2, C100.2, C101.2, C102.2, C103.2, C104.2, C105.2, C106.2, C107.2, C108.2, C109.2, C110.2, C111.2, C112.2, C113.2, C114.2, D28.C, D30.C, J36.GND, J36.GND2, J36.SHLD1, J36.SHLD2, J36.SHLD3, J36.SHLD4, J37.1, J38.1, J40.13, J41.3, J41.5, J41.9, J42.CD1, J42.GND, J42.GND1, J42.GND3, R61.1, R62.1, R66.1, R67.1, S11.3, S11.4, U21.12, U21.18, U21.28, U21.63, U22.2, U23.2, U24.4
GND6: C115.2, C116.2, C117.2, C118.2, C119.2, C120.2, C121.2, C122.2, C123.2, C124.2, C125.2, C126.2, C127.2, C128.2, C129.2, C130.2, C131.2, C132.2, C133.2, D33.C, D35.C, J43.GND, J43.GND2, J43.SHLD1, J43.SHLD2, J43.SHLD3, J43.SHLD4, J44.1, J45.1, J47.13, J48.3, J48.5, J48.9, J49.CD1, J49.GND, J49.GND1, J49.GND3, R73.1, R74.1, R78.1, R79.1, S13.3, S13.4, U25.12, U25.18, U25.28, U25.63, U26.2, U27.2, U28.4
GND7: C134.2, C135.2, C136.2, C137.2, C138.2, C139.2, C140.2, C141.2, C142.2, C143.2, C144.2, C145.2, C146.2, C147.2, C148.2, C149.2, C150.2, C151.2, C152.2, D38.C, D40.C, J50.GND, J50.GND2, J50.SHLD1, J50.SHLD2, J50.SHLD3, J50.SHLD4, J51.1, J52.1, J54.13, J55.3, J55.5, J55.9, J56.CD1, J56.GND, J56.GND1, J56.GND3, R85.1, R86.1, R90.1, R91.1, S15.3, S15.4, U29.12, U29.18, U29.28, U29.63, U30.2, U31.2, U32.4
GND8: C153.2, C154.2, C155.2, C156.2, C157.2, C158.2, C159.2, C160.2, C161.2, C162.2, C163.2, C164.2, C165.2, C166.2, C167.2, C168.2, C169.2, C170.2, C171.2, D43.C, D45.C, J57.GND, J57.GND2, J57.SHLD1, J57.SHLD2, J57.SHLD3, J57.SHLD4, J58.1, J59.1, J61.13, J62.3, J62.5, J62.9, J63.CD1, J63.GND, J63.GND1, J63.GND3, R97.1, R98.1, R102.1, R103.1, S17.3, S17.4, U33.12, U33.18, U33.28, U33.63, U34.2, U35.2, U36.4
GND9: C172.2, C173.2, C174.2, C175.2, C176.2, C177.2, C178.2, C179.2, C180.2, C181.2, C182.2, C183.2, C184.2, C185.2, C186.2, C187.2, C188.2, C189.2, C190.2, D48.C, D50.C, J64.GND, J64.GND2, J64.SHLD1, J64.SHLD2, J64.SHLD3, J64.SHLD4, J65.1, J66.1, J68.13, J69.3, J69.5, J69.9, J70.CD1, J70.GND, J70.GND1, J70.GND3, R109.1, R110.1, R114.1, R115.1, S19.3, S19.4, U37.12, U37.18, U37.28, U37.63, U38.2, U39.2, U40.4
GND10: C191.2, C192.2, C193.2, C194.2, C195.2, C196.2, C197.2, C198.2, C199.2, C200.2, C201.2, C202.2, C203.2, C204.2, C205.2, C206.2, C207.2, C208.2, C209.2, D53.C, D55.C, J71.GND, J71.GND2, J71.SHLD1, J71.SHLD2, J71.SHLD3, J71.SHLD4, J72.1, J73.1, J75.13, J76.3, J76.5, J76.9, J77.CD1, J77.GND, J77.GND1, J77.GND3, R121.1, R122.1, R126.1, R127.1, S21.3, S21.4, U41.12, U41.18, U41.28, U41.63, U42.2, U43.2, U44.4
GND11: C210.2, C211.2, C212.2, C213.2, C214.2, C215.2, C216.2, C217.2, C218.2, C219.2, C220.2, C221.2, C222.2, C223.2, C224.2, C225.2, C226.2, C227.2, C228.2, D58.C, D60.C, J78.GND, J78.GND2, J78.SHLD1, J78.SHLD2, J78.SHLD3, J78.SHLD4, J79.1, J80.1, J82.13, J83.3, J83.5, J83.9, J84.CD1, J84.GND, J84.GND1, J84.GND3, R133.1, R134.1, R138.1, R139.1, S23.3, S23.4, U45.12, U45.18, U45.28, U45.63, U46.2, U47.2, U48.4
GND12: C229.2, C230.2, C231.2, C232.2, C233.2, C234.2, C235.2, C236.2, C237.2, C238.2, C239.2, C240.2, C241.2, C242.2, C243.2, C244.2, C245.2, C246.2, C247.2, D63.C, D65.C, J85.GND, J85.GND2, J85.SHLD1, J85.SHLD2, J85.SHLD3, J85.SHLD4, J86.1, J87.1, J89.13, J90.3, J90.5, J90.9, J91.CD1, J91.GND, J91.GND1, J91.GND3, R145.1, R146.1, R150.1, R151.1, S25.3, S25.4, U49.12, U49.18, U49.28, U49.63, U50.2, U51.2, U52.4
GND13: C248.2, C249.2, C250.2, C251.2, C252.2, C253.2, C254.2, C255.2, C256.2, C257.2, C258.2, C259.2, C260.2, C261.2, C262.2, C263.2, C264.2, C265.2, C266.2, D68.C, D70.C, J92.GND, J92.GND2, J92.SHLD1, J92.SHLD2, J92.SHLD3, J92.SHLD4, J93.1, J94.1, J96.13, J97.3, J97.5, J97.9, J98.CD1, J98.GND, J98.GND1, J98.GND3, R157.1, R158.1, R162.1, R163.1, S27.3, S27.4, U53.12, U53.18, U53.28, U53.63, U54.2, U55.2, U56.4
GND14: C267.2, C268.2, C269.2, C270.2, C271.2, C272.2, C273.2, C274.2, C275.2, C276.2, C277.2, C278.2, C279.2, C280.2, C281.2, C282.2, C283.2, C284.2, C285.2, D73.C, D75.C, J99.GND, J99.GND2, J99.SHLD1, J99.SHLD2, J99.SHLD3, J99.SHLD4, J100.1, J101.1, J103.13, J104.3, J104.5, J104.9, J105.CD1, J105.GND, J105.GND1, J105.GND3, R169.1, R170.1, R174.1, R175.1, S29.3, S29.4, U57.12, U57.18, U57.28, U57.63, U58.2, U59.2, U60.4
unnamed: D5.A, R12.1
unnamed: PWR.1, R4.2
unnamed: J1.A6, J1.B6, R9.1
unnamed: J8.A5, R14.2
unnamed: J8.B5, R13.2
unnamed: J1.A7, J1.B7, R10.1
unnamed: D3.A, R4.1
unnamed: R6.2, U1.5
unnamed: J1.A5, R2.2
unnamed: J1.B5, R1.2
unnamed: D8.A, R16.1
unnamed: R18.2, U6.5
unnamed: D9.C, R17.2
unnamed: D4.C, R5.2
unnamed: R5.1, U1.1
unnamed: C5.1, U4.31
unnamed: R17.1, U6.1
unnamed: C6.1, U4.47
unnamed: C24.1, U5.31
unnamed: C25.1, U5.47
unnamed: J8.A6, J8.B6, R21.1
unnamed: J8.A7, J8.B7, R22.1
unnamed: D10.A, R24.1
unnamed: PWR1.1, R16.2
unnamed: J15.A5, R26.2
unnamed: J15.B5, R25.2
unnamed: D13.A, R28.1
unnamed: R30.2, U10.5
unnamed: D14.C, R29.2
unnamed: R29.1, U10.1
unnamed: C43.1, U9.31
unnamed: C44.1, U9.47
unnamed: J15.A6, J15.B6, R33.1
unnamed: J15.A7, J15.B7, R34.1
unnamed: D15.A, R36.1
unnamed: PWR2.1, R28.2
unnamed: J22.A5, R38.2
unnamed: J22.B5, R37.2
unnamed: D18.A, R40.1
unnamed: R42.2, U14.5
unnamed: D19.C, R41.2
unnamed: R41.1, U14.1
unnamed: C62.1, U13.31
unnamed: C63.1, U13.47
unnamed: J22.A6, J22.B6, R45.1
unnamed: J22.A7, J22.B7, R46.1
unnamed: D20.A, R48.1
unnamed: PWR3.1, R40.2
unnamed: J29.A5, R50.2
unnamed: J29.B5, R49.2
unnamed: D23.A, R52.1
unnamed: R54.2, U18.5
unnamed: D24.C, R53.2
unnamed: R53.1, U18.1
unnamed: C81.1, U17.31
unnamed: C82.1, U17.47
unnamed: J29.A6, J29.B6, R57.1
unnamed: J29.A7, J29.B7, R58.1
unnamed: D25.A, R60.1
unnamed: PWR4.1, R52.2
unnamed: J36.A5, R62.2
unnamed: J36.B5, R61.2
unnamed: D28.A, R64.1
unnamed: R66.2, U22.5
unnamed: D29.C, R65.2
unnamed: R65.1, U22.1
unnamed: C100.1, U21.31
unnamed: C101.1, U21.47
unnamed: J36.A6, J36.B6, R69.1
unnamed: J36.A7, J36.B7, R70.1
unnamed: D30.A, R72.1
unnamed: PWR5.1, R64.2
unnamed: J43.A5, R74.2
unnamed: J43.B5, R73.2
unnamed: D33.A, R76.1
unnamed: R78.2, U26.5
unnamed: D34.C, R77.2
unnamed: R77.1, U26.1
unnamed: C119.1, U25.31
unnamed: C120.1, U25.47
unnamed: J43.A6, J43.B6, R81.1
unnamed: J43.A7, J43.B7, R82.1
unnamed: D35.A, R84.1
unnamed: PWR6.1, R76.2
unnamed: J50.A5, R86.2
unnamed: J50.B5, R85.2
unnamed: D38.A, R88.1
unnamed: R90.2, U30.5
unnamed: D39.C, R89.2
unnamed: R89.1, U30.1
unnamed: C138.1, U29.31
unnamed: C139.1, U29.47
unnamed: J50.A6, J50.B6, R93.1
unnamed: J50.A7, J50.B7, R94.1
unnamed: D40.A, R96.1
unnamed: PWR7.1, R88.2
unnamed: J57.A5, R98.2
unnamed: J57.B5, R97.2
unnamed: D43.A, R100.1
unnamed: R102.2, U34.5
unnamed: D44.C, R101.2
unnamed: R101.1, U34.1
unnamed: C157.1, U33.31
unnamed: C158.1, U33.47
unnamed: J57.A6, J57.B6, R105.1
unnamed: J57.A7, J57.B7, R106.1
unnamed: D45.A, R108.1
unnamed: PWR8.1, R100.2
unnamed: J64.A5, R110.2
unnamed: J64.B5, R109.2
unnamed: D48.A, R112.1
unnamed: R114.2, U38.5
unnamed: D49.C, R113.2
unnamed: R113.1, U38.1
unnamed: C176.1, U37.31
unnamed: C177.1, U37.47
unnamed: J64.A6, J64.B6, R117.1
unnamed: J64.A7, J64.B7, R118.1
unnamed: D50.A, R120.1
unnamed: PWR9.1, R112.2
unnamed: J71.A5, R122.2
unnamed: J71.B5, R121.2
unnamed: D53.A, R124.1
unnamed: R126.2, U42.5
unnamed: D54.C, R125.2
unnamed: R125.1, U42.1
unnamed: C195.1, U41.31
unnamed: C196.1, U41.47
unnamed: J71.A6, J71.B6, R129.1
unnamed: J71.A7, J71.B7, R130.1
unnamed: D55.A, R132.1
unnamed: PWR10.1, R124.2
unnamed: J78.A5, R134.2
unnamed: J78.B5, R133.2
unnamed: D58.A, R136.1
unnamed: R138.2, U46.5
unnamed: D59.C, R137.2
unnamed: R137.1, U46.1
unnamed: C214.1, U45.31
unnamed: C215.1, U45.47
unnamed: J78.A6, J78.B6, R141.1
unnamed: J78.A7, J78.B7, R142.1
unnamed: D60.A, R144.1
unnamed: PWR11.1, R136.2
unnamed: J85.A5, R146.2
unnamed: J85.B5, R145.2
unnamed: D63.A, R148.1
unnamed: R150.2, U50.5
unnamed: D64.C, R149.2
unnamed: R149.1, U50.1
unnamed: C233.1, U49.31
unnamed: C234.1, U49.47
unnamed: J85.A6, J85.B6, R153.1
unnamed: J85.A7, J85.B7, R154.1
unnamed: D65.A, R156.1
unnamed: PWR12.1, R148.2
unnamed: J92.A5, R158.2
unnamed: J92.B5, R157.2
unnamed: D68.A, R160.1
unnamed: R162.2, U54.5
unnamed: D69.C, R161.2
unnamed: R161.1, U54.1
unnamed: C252.1, U53.31
unnamed: C253.1, U53.47
unnamed: J92.A6, J92.B6, R165.1
unnamed: J92.A7, J92.B7, R166.1
unnamed: D70.A, R168.1
unnamed: PWR13.1, R160.2
unnamed: J99.A5, R170.2
unnamed: J99.B5, R169.2
unnamed: D73.A, R172.1
unnamed: R174.2, U58.5
unnamed: D74.C, R173.2
unnamed: R173.1, U58.1
unnamed: C271.1, U57.31
unnamed: C272.1, U57.47
unnamed: J99.A6, J99.B6, R177.1
unnamed: J99.A7, J99.B7, R178.1
unnamed: D75.A, R180.1
unnamed: PWR14.1, R172.2
OSC_IN: C18.1, U4.5, Y2.1
OSC_IN1: C37.1, U5.5, Y4.1
OSC_IN2: C56.1, U9.5, Y6.1
OSC_IN3: C75.1, U13.5, Y8.1
OSC_IN4: C94.1, U17.5, Y10.1
OSC_IN5: C113.1, U21.5, Y12.1
OSC_IN6: C132.1, U25.5, Y14.1
OSC_IN7: C151.1, U29.5, Y16.1
OSC_IN8: C170.1, U33.5, Y18.1
OSC_IN9: C189.1, U37.5, Y20.1
OSC_IN10: C208.1, U41.5, Y22.1
OSC_IN11: C227.1, U45.5, Y24.1
OSC_IN12: C246.1, U49.5, Y26.1
OSC_IN13: C265.1, U53.5, Y28.1
OSC_IN14: C284.1, U57.5, Y30.1
OSC_OUT: C19.1, U4.6, Y2.3
OSC_OUT1: C38.1, U5.6, Y4.3
OSC_OUT2: C57.1, U9.6, Y6.3
OSC_OUT3: C76.1, U13.6, Y8.3
OSC_OUT4: C95.1, U17.6, Y10.3
OSC_OUT5: C114.1, U21.6, Y12.3
OSC_OUT6: C133.1, U25.6, Y14.3
OSC_OUT7: C152.1, U29.6, Y16.3
OSC_OUT8: C171.1, U33.6, Y18.3
OSC_OUT9: C190.1, U37.6, Y20.3
OSC_OUT10: C209.1, U41.6, Y22.3
OSC_OUT11: C228.1, U45.6, Y24.3
OSC_OUT12: C247.1, U49.6, Y26.3
OSC_OUT13: C266.1, U53.6, Y28.3
OSC_OUT14: C285.1, U57.6, Y30.3
SCK: J5.6, U4.34
SCK1: J12.6, U5.34
SCK2: J19.6, U9.34
SCK3: J26.6, U13.34
SCK4: J33.6, U17.34
SCK5: J40.6, U21.34
SCK6: J47.6, U25.34
SCK7: J54.6, U29.34
SCK8: J61.6, U33.34
SCK9: J68.6, U37.34
SCK10: J75.6, U41.34
SCK11: J82.6, U45.34
SCK12: J89.6, U49.34
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
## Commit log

2020-12-07 Updated V01
2021-01-28 Updated version number to V10
2021-02-01 V10 design review changes
    Replaced V_BAT pin connection on STM32 to test point
    Moved microSD connector to center card on PCB instead of footprint
    Removed overlapping labels on bottom
2021-02-02 Double-check changes
    Schematic
    - Added VDD range
    - Added RTC Battery range
    Board
    - Updated labels
2021-02-02 added production panel
2021-02-03 Updated Panel
2021-03-29 BOM update
    Replaced 22 ohm resistors with 0 ohm
    Replaced old momentary switches to taller momentary switches
2021-04-12 Updated USB Load Resistors
    Switch 0 ohm resistors back to 22 ohm
